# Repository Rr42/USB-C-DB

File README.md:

# USB-C display board for Micro-controllers
This is a mini display board with a USB Type-C connector (carrying USB 2.0) and an onboard micro-controller.

The goal of this display board is to test and evaluate:
* The USB-C interface for a Micro-controller
    * This design uses ESP-WROOM-02
* (TENTATIVE) Implementation of an onboard battery to power the board when disconnected from power
* (TENTATIVE) Onboard battery charging capability using USB-C

## Design overview
### Connecting and booting
To connect to the display board, simply connect it to power and connect to the WiFi network `USB-C DB` it hosts.

Once connected navigate to [http://192.168.1.1](http://192.168.1.1/) and click/press `Play boot animation`.

Once the boot animation plays the page will reload with all the functions enabled.

## Power consumption
The USB-C display board consumes anywhere from `450mW` to a maximum of `800mW` depending on the brightness level from 5V USB.
> Note that the display board does not have the capability and will not negotiate to any of the higher voltage levels offered by USB PD

For context a `500mAh` battery will be able to power the display board for about `3.5 hours` (with maximum power level of `800mW`) and about `5.5 hours` (at the lower `450mW` power level).

### Main page

### Display controller hierarchy

## License
The Software and firmware of this project is licensed under the the MIT license and the hardware is under the [Open Source Hardware](https://www.oshwa.org/definition/) license.

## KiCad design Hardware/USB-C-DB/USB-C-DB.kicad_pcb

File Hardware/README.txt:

# Read me for the USB-C display board hardware
This is a mini display board with a USB Type-C connector (carrying USB 2.0) and an onboard micro-controller.

This project is created using KiCAD (v5.1.10).

The goal of this display board is to test and evaluate:
* The USB-C interface for a Micro-controller
    * This design uses ESP-WROOM-02
* (TENTATIVE) Implementation of an onboard battery to power the board when disconnected from power
* (TENTATIVE) Onboard battery charging capability using USB-C

## License
The Software and firmware of this project is licensed under the the MIT license however the hardware is under the [Open Source Hardware](https://www.oshwa.org/definition/) license.

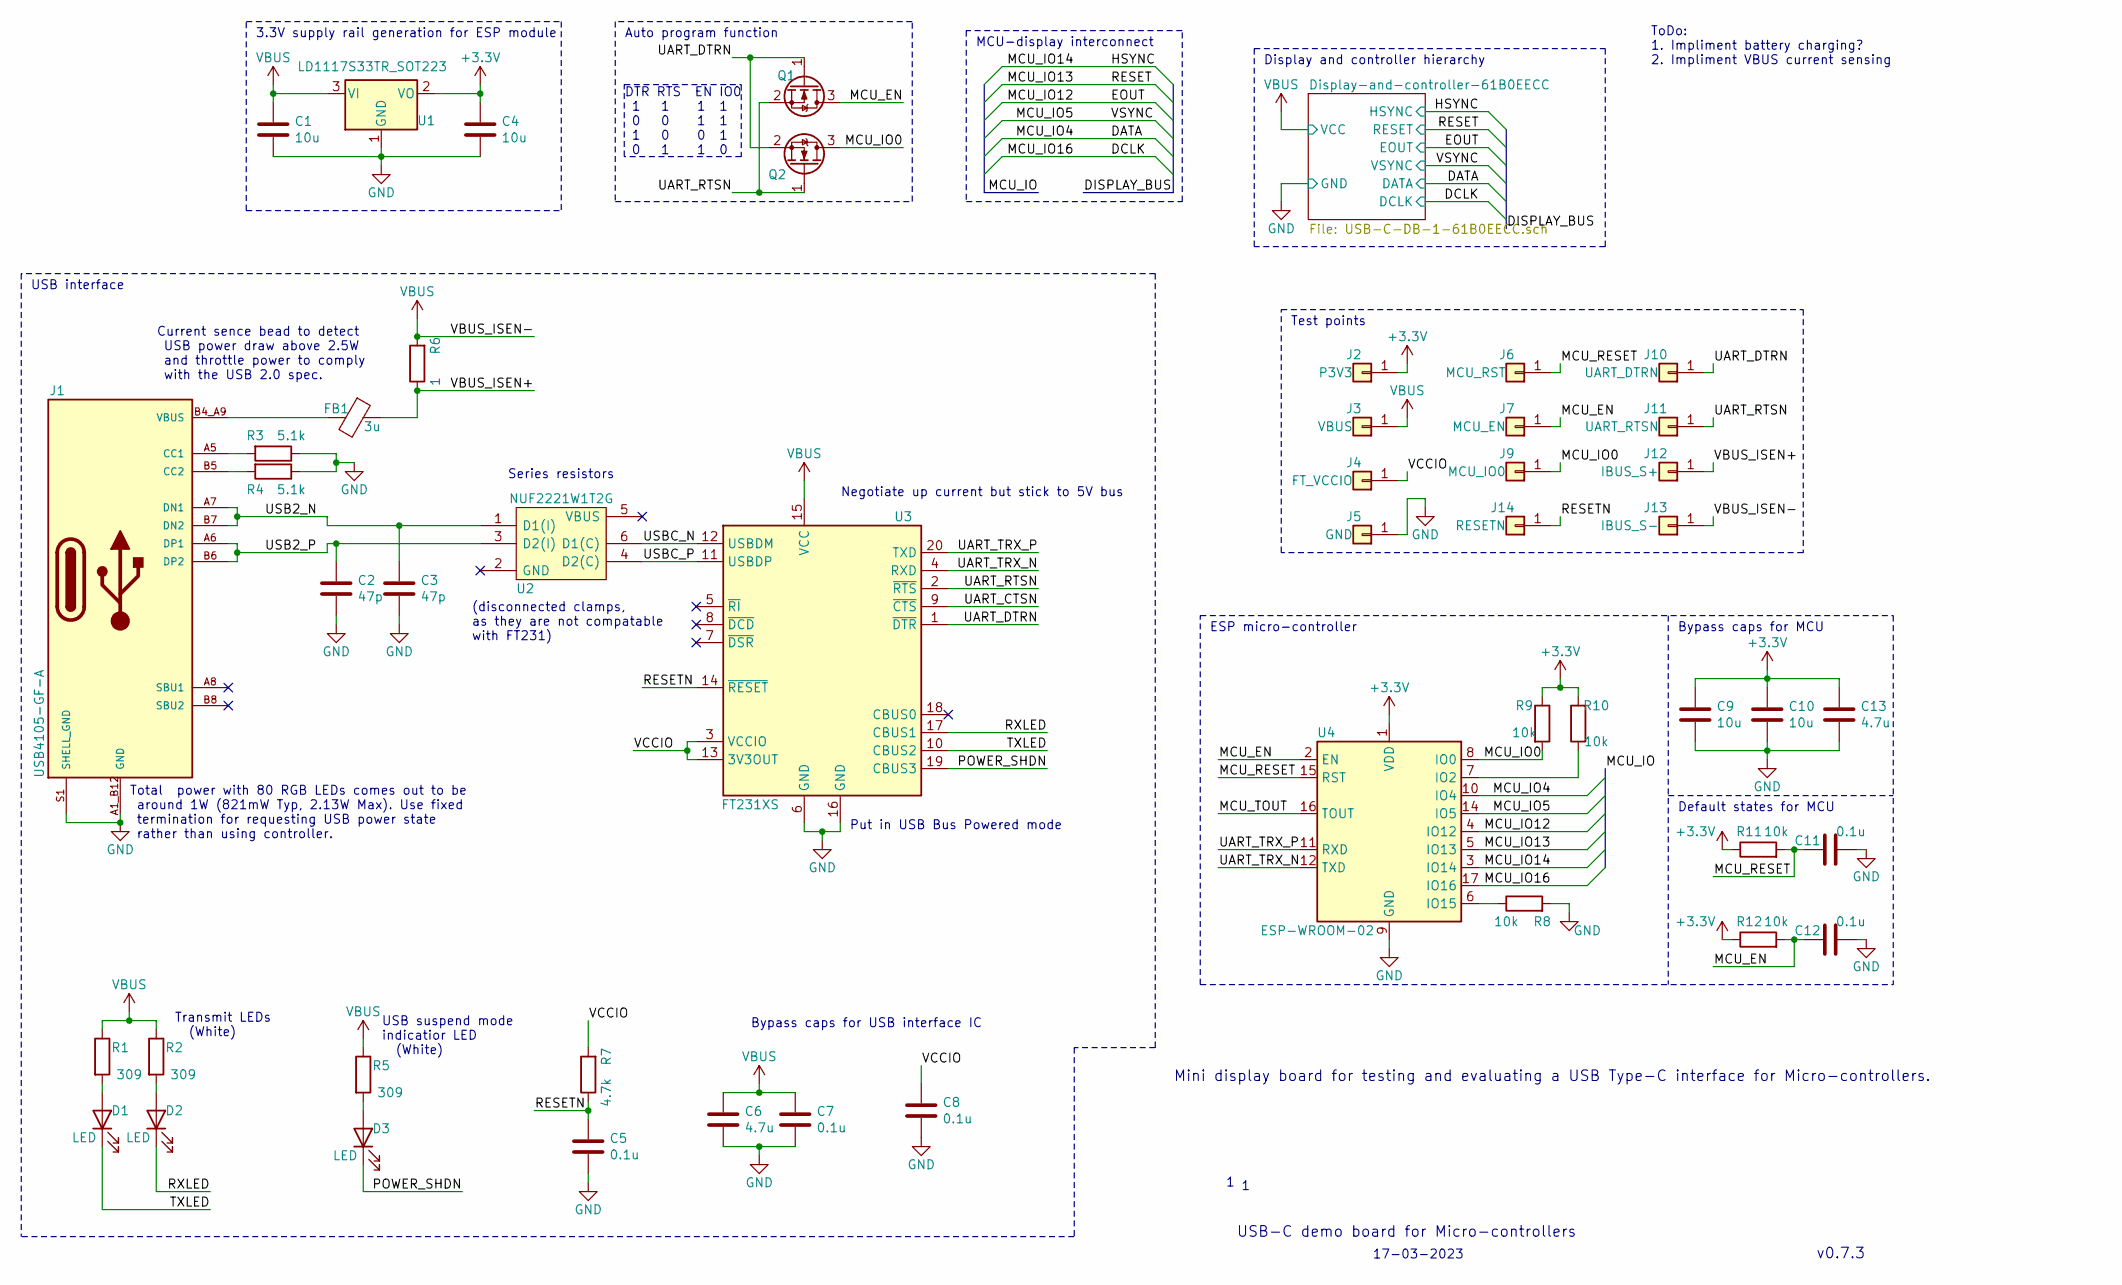
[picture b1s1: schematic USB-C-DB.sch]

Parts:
C1, C4, C9, C10: 10u; C_0805_2012Metric_Pad1.18x1.45mm_HandSolder; MPN CL21A106KOQNNNE
C2, C3: 47p; C_0402_1005Metric_Pad0.74x0.62mm_HandSolder; MPN C0402C470J5GAC
C5, C7, C8, C11, C12: 0.1u; C_0805_2012Metric_Pad1.18x1.45mm_HandSolder; MPN C0805C104M5RAC
C6, C13: 4.7u; C_0805_2012Metric_Pad1.18x1.45mm_HandSolder; MPN CL21A475KAQNNNF
D1, D2, D3: LED; LED_Cree-PLCC4_3.2x2.8mm_CCW; MPN CLA1A-WKB-CWbYa153
FB1: 3u; R_0603_1608Metric_Pad0.98x0.95mm_HandSolder; MPN KPZ1608SHR601ATD25
J1: USB4105-GF-A; GCT_USB4105-GF-A; PARTREV A3
J2: P3V3; TestPoint_Pad_D1.0mm
J3: VBUS; TestPoint_Pad_D1.0mm
J4: FT_VCCIO; TestPoint_Pad_D1.0mm
J5: GND; TestPoint_Pad_D1.0mm
J6: MCU_RST; TestPoint_Pad_D1.0mm
J7: MCU_EN; TestPoint_Pad_D1.0mm
J9: MCU_IO0; TestPoint_Pad_D1.0mm
J10: UART_DTRN; TestPoint_Pad_D1.0mm
J11: UART_RTSN; TestPoint_Pad_D1.0mm
J12: IBUS_S+; TestPoint_Pad_D1.0mm
J13: IBUS_S-; TestPoint_Pad_D1.0mm
J14: RESETN; TestPoint_Pad_D1.0mm
Q1, Q2: XP262N7002TR-G; SOT-23; MPN XP262N7002TR-G
R1, R2, R5: 309; R_0603_1608Metric_Pad0.98x0.95mm_HandSolder; MPN RC0603FR-07309RL
R3, R4: 5.1k; R_0805_2012Metric_Pad1.20x1.40mm_HandSolder; MPN TR0805KR-075K1L
R6: 1; R_0603_1608Metric_Pad0.98x0.95mm_HandSolder; MPN RT0603DRE071RL
R7: 4.7k; R_0805_2012Metric_Pad1.20x1.40mm_HandSolder; MPN RC0805FR-074K7P
R8, R9, R10, R11, R12: 10k; R_0603_1608Metric_Pad0.98x0.95mm_HandSolder; MPN CRG0603F10K/10
U1: LD1117S33TR_SOT223; SOT-223-3_TabPin2; MPN LD1117S33CTR
U2: NUF2221W1T2G; SOT65P210X110-6N; Mouser Part Number 863-NUF2221W1T2G
U3: FT231XS; SSOP-20_3.9x8.7mm_P0.635mm; MPN FT231XS-R; Mouser Part Number 895-FT231XS-R
U4: ESP-WROOM-02; MPN ESP-WROOM-02D-N2

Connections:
+3V3: C4.1, C9.1, C10.1, C13.1, J2.1, R9.1, R10.2, R11.1, R12.1, U1.2 (VO), U4.1 (VDD)
/DATA: U4.10 (IO4); also elsewhere on the board
/DCLK: U4.17 (IO16); also elsewhere on the board
/EOUT: U4.4 (IO12); also elsewhere on the board
/HSYNC: U4.3 (IO14); also elsewhere on the board
/MCU_EN: C12.1, J7.1, Q1.3 (D), R12.2, U4.2 (EN)
/MCU_IO0: J9.1, Q2.3 (D), R9.2, U4.8 (IO0)
/MCU_IO5: U4.14 (IO5); also elsewhere on the board
/MCU_IO13: U4.5 (IO13); also elsewhere on the board
/MCU_RESET: C11.1, J6.1, R11.2, U4.15 (RST)
/MCU_TOUT: U4.16 (TOUT)
/POWER_SHDN: D3.4 (K), U3.19 (CBUS3)
/RESETN: C5.1, J14.1, R7.1, U3.14 (~RESET)
/RXLED: D2.4 (K), U3.17 (CBUS1)
/TXLED: D1.4 (K), U3.10 (CBUS2)
/UART_CTSN: U3.9 (~CTS)
/UART_DTRN: J10.1, Q1.1 (G), Q2.2 (S), U3.1 (~DTR)
/UART_RTSN: J11.1, Q1.2 (S), Q2.1 (G), U3.2 (~RTS)
/UART_TRX_N: U3.4 (RXD), U4.12 (TXD)
/UART_TRX_P: U3.20 (TXD), U4.11 (RXD)
/USB2_N: C3.1, J1.A7 (DN1), J1.B7 (DN2), U2.1 (D1(I))
/USB2_P: C2.1, J1.A6 (DP1), J1.B6 (DP2), U2.3 (D2(I))
/USBC_N: U2.6 (D1(C)), U3.12 (USBDM)
/USBC_P: U2.4 (D2(C)), U3.11 (USBDP)
/VBUS_ISEN+: FB1.1, J12.1, R6.1
/VCCIO: C8.1, J4.1, R7.2, U3.3 (VCCIO), U3.13 (3V3OUT)
GND: C1.2, C2.2, C3.2, C4.2, C5.2, C6.2, C7.2, C8.2, C9.2, C10.2, C11.2, C12.2, C13.2, J1.A1_B12 (GND), J1.B1_A12 (GND), J1.S1 (SHELL_GND), J1.S2 (SHELL_GND), J1.S3 (SHELL_GND), J1.S4 (SHELL_GND), J5.1, R3.1, R4.1, R8.2, U1.1 (GND), U3.6 (GND), U3.16 (GND), U4.9 (GND), U4.13 (GND), U4.18 (GND), U4.19 (GND); also elsewhere on the board
unnamed: D1.2 (A), R1.2
unnamed: D2.2 (A), R2.2
unnamed: D3.2 (A), R5.2
unnamed: J1.A5 (CC1), R3.2
unnamed: J1.B5 (CC2), R4.2
unnamed: R8.1, U4.6 (IO15)
unnamed: R10.1, U4.7 (IO2)

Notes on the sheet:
USB-C demo board for Micro-controllers
v0.7.3
17-03-2023
Mini display board for testing and evaluating a USB Type-C interface for Micro-controllers.
Total power with 80 RGB LEDs comes out to be around 1W (821mW Typ, 2.13W Max). Use fixed termination for requesting USB power state rather than using controller.
Current sence bead to detect USB power draw above 2.5W and throttle power to comply with the USB 2.0 spec.
Display and controller hierarchy
Series resistors
Bypass caps for USB interface IC
USB interface
Auto program function
DTR RTS EN IO0 1 1 1 1 0 0 1 1 1 0 0 1 0 1 1 0
MCU-display interconnect
3.3V supply rail generation for ESP module
Test points
Default states for MCU
ESP micro-controller
Bypass caps for MCU
ToDo: 1. Impliment battery charging? 2. Impliment VBUS current sensing
Negotiate up current but stick to 5V bus
Put in USB Bus Powered mode
Transmit LEDs (White)
USB suspend mode indicatior LED (White)
(disconnected clamps, as they are not compatable with FT231)

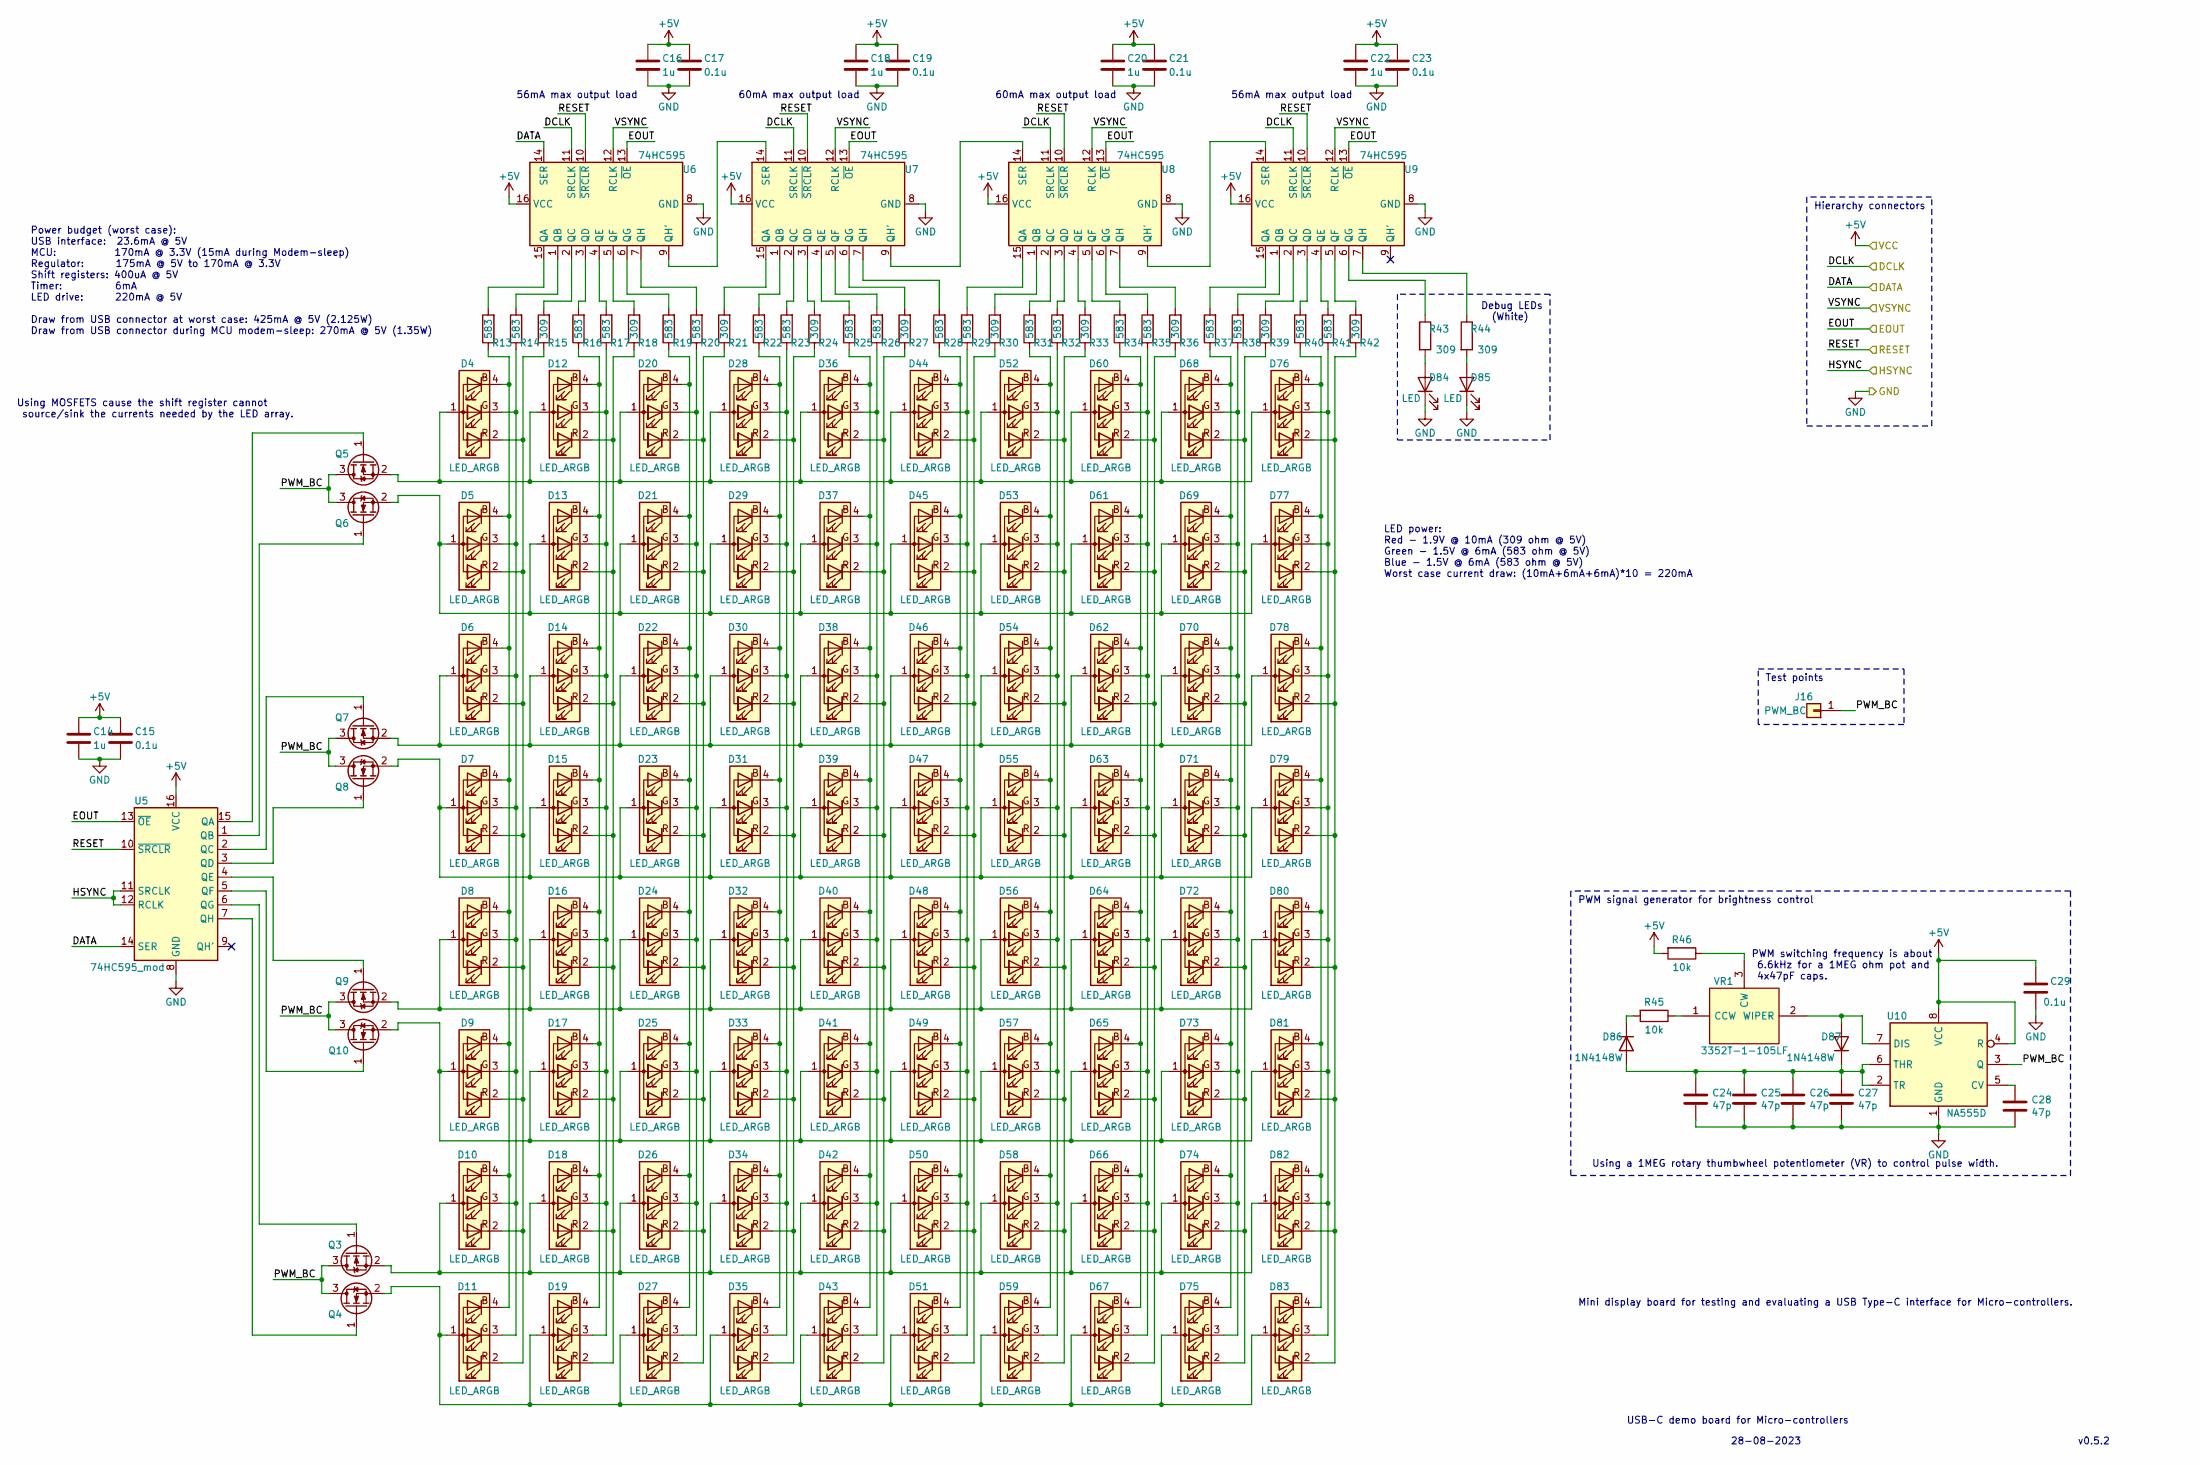
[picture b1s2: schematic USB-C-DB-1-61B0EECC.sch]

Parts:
C14, C16, C18, C20, C22: 1u; C_0805_2012Metric_Pad1.18x1.45mm_HandSolder; MPN CL21B105KBFNNNG
C15, C17, C19, C21, C23, C29: 0.1u; C_0805_2012Metric_Pad1.18x1.45mm_HandSolder; MPN C0805C104M5RAC
C24, C25, C26, C27, C28: 47p; C_0402_1005Metric_Pad0.74x0.62mm_HandSolder; MPN C0402C470J5GAC
D4, D5, D6, D7, D8, D9, D10, D11, D12, D13, D14, D15, D16, D17, D18, D19, D20, D21, D22, D23, D24, D25, D26, D27, D28, D29, D30, D31, D32, D33, D34, D35, D36, D37, D38, D39, D40, D41, D42, D43, D44, D45, D46, D47, D48, D49, D50, D51, D52, D53, D54, D55, D56, D57, D58, D59, D60, D61, D62, D63, D64, D65, D66, D67, D68, D69, D70, D71, D72, D73, D74, D75, D76, D77, D78, D79, D80, D81, D82, D83: LED_ARGB; LED_Cree-PLCC4_3.2x2.8mm_CCW; MPN CLV1L-FKB-CJ1N1E1BB7B3B3
D84, D85: LED; LED_Cree-PLCC4_3.2x2.8mm_CCW; MPN CLA1A-WKB-CWbYa153
D86, D87: 1N4148W; D_SOD-123; MPN 1N4148W_R1_00001
J16: PWM_BC; TestPoint_Pad_D1.0mm
Q3, Q4, Q5, Q6, Q7, Q8, Q9, Q10: XP262N7002TR-G; SOT-23; MPN XP262N7002TR-G
R13, R14, R16, R17, R19, R20, R22, R23, R25, R26, R28, R29, R31, R32, R34, R35, R37, R38, R40, R41: 583; R_0603_1608Metric_Pad0.98x0.95mm_HandSolder; MPN RT0603DRE07583RL
R15, R18, R21, R24, R27, R30, R33, R36, R39, R42, R43, R44: 309; R_0603_1608Metric_Pad0.98x0.95mm_HandSolder; MPN RC0603FR-07309RL
R45, R46: 10k; R_0603_1608Metric_Pad0.98x0.95mm_HandSolder; MPN CRG0603F10K/10
U5: 74HC595_mod; TSSOP-16_4.4x5mm_P0.65mm; MPN MC74HC595ADTG
U6, U7, U8, U9: 74HC595; TSSOP-16_4.4x5mm_P0.65mm; MPN MC74HC595ADTG
U10: NA555D; SOIC-8_3.9x4.9mm_P1.27mm; MPN NA555DR
VR1: 3352T-1-105LF; 3352T1103LF; Mouser Part Number 652-3352T-1-105LF

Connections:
/DATA: U5.14 (SER), U6.14 (SER); also elsewhere on the board
/DCLK: U6.11 (SRCLK), U7.11 (SRCLK), U8.11 (SRCLK), U9.11 (SRCLK); also elsewhere on the board
/Display-and-controller-61B0EECC/PWM_BC: J16.1, Q3.3 (D), Q4.3 (D), Q5.3 (D), Q6.3 (D), Q7.3 (D), Q8.3 (D), Q9.3 (D), Q10.3 (D), U10.3 (Q)
/EOUT: U5.13 (~OE), U6.13 (~OE), U7.13 (~OE), U8.13 (~OE), U9.13 (~OE); also elsewhere on the board
/HSYNC: U5.11 (SRCLK), U5.12 (RCLK); also elsewhere on the board
/MCU_IO5: U6.12 (RCLK), U7.12 (RCLK), U8.12 (RCLK), U9.12 (RCLK); also elsewhere on the board
/MCU_IO13: U5.10 (~SRCLR), U6.10 (~SRCLR), U7.10 (~SRCLR), U8.10 (~SRCLR), U9.10 (~SRCLR); also elsewhere on the board
GND: C14.2, C15.2, C16.2, C17.2, C18.2, C19.2, C20.2, C21.2, C22.2, C23.2, C24.2, C25.2, C26.2, C27.2, C28.2, C29.2, D84.4 (K), D85.4 (K), U5.8 (GND), U6.8 (GND), U7.8 (GND), U8.8 (GND), U9.8 (GND), U10.1 (GND); also elsewhere on the board
unnamed: C24.1, C25.1, C26.1, C27.1, D86.2 (A), D87.1 (K), U10.2 (TR), U10.6 (THR)
unnamed: C28.1, U10.5 (CV)
unnamed: D10.1 (A), D18.1 (A), D26.1 (A), D34.1 (A), D42.1 (A), D50.1 (A), D58.1 (A), D66.1 (A), D74.1 (A), D82.1 (A), Q3.2 (S)
unnamed: D4.2 (RK), D5.2 (RK), D6.2 (RK), D7.2 (RK), D8.2 (RK), D9.2 (RK), D10.2 (RK), D11.2 (RK), R15.1
unnamed: D4.3 (GK), D5.3 (GK), D6.3 (GK), D7.3 (GK), D8.3 (GK), D9.3 (GK), D10.3 (GK), D11.3 (GK), R14.1
unnamed: D4.4 (BK), D5.4 (BK), D6.4 (BK), D7.4 (BK), D8.4 (BK), D9.4 (BK), D10.4 (BK), D11.4 (BK), R13.1
unnamed: D11.1 (A), D19.1 (A), D27.1 (A), D35.1 (A), D43.1 (A), D51.1 (A), D59.1 (A), D67.1 (A), D75.1 (A), D83.1 (A), Q4.2 (S)
unnamed: D4.1 (A), D12.1 (A), D20.1 (A), D28.1 (A), D36.1 (A), D44.1 (A), D52.1 (A), D60.1 (A), D68.1 (A), D76.1 (A), Q5.2 (S)
unnamed: D12.2 (RK), D13.2 (RK), D14.2 (RK), D15.2 (RK), D16.2 (RK), D17.2 (RK), D18.2 (RK), D19.2 (RK), R18.1
unnamed: D12.3 (GK), D13.3 (GK), D14.3 (GK), D15.3 (GK), D16.3 (GK), D17.3 (GK), D18.3 (GK), D19.3 (GK), R17.1
unnamed: D12.4 (BK), D13.4 (BK), D14.4 (BK), D15.4 (BK), D16.4 (BK), D17.4 (BK), D18.4 (BK), D19.4 (BK), R16.1
unnamed: D5.1 (A), D13.1 (A), D21.1 (A), D29.1 (A), D37.1 (A), D45.1 (A), D53.1 (A), D61.1 (A), D69.1 (A), D77.1 (A), Q6.2 (S)
unnamed: D6.1 (A), D14.1 (A), D22.1 (A), D30.1 (A), D38.1 (A), D46.1 (A), D54.1 (A), D62.1 (A), D70.1 (A), D78.1 (A), Q7.2 (S)
unnamed: D7.1 (A), D15.1 (A), D23.1 (A), D31.1 (A), D39.1 (A), D47.1 (A), D55.1 (A), D63.1 (A), D71.1 (A), D79.1 (A), Q8.2 (S)
unnamed: D8.1 (A), D16.1 (A), D24.1 (A), D32.1 (A), D40.1 (A), D48.1 (A), D56.1 (A), D64.1 (A), D72.1 (A), D80.1 (A), Q9.2 (S)
unnamed: D9.1 (A), D17.1 (A), D25.1 (A), D33.1 (A), D41.1 (A), D49.1 (A), D57.1 (A), D65.1 (A), D73.1 (A), D81.1 (A), Q10.2 (S)
unnamed: D20.2 (RK), D21.2 (RK), D22.2 (RK), D23.2 (RK), D24.2 (RK), D25.2 (RK), D26.2 (RK), D27.2 (RK), R21.1
unnamed: D20.3 (GK), D21.3 (GK), D22.3 (GK), D23.3 (GK), D24.3 (GK), D25.3 (GK), D26.3 (GK), D27.3 (GK), R20.1
unnamed: D20.4 (BK), D21.4 (BK), D22.4 (BK), D23.4 (BK), D24.4 (BK), D25.4 (BK), D26.4 (BK), D27.4 (BK), R19.1
unnamed: D28.2 (RK), D29.2 (RK), D30.2 (RK), D31.2 (RK), D32.2 (RK), D33.2 (RK), D34.2 (RK), D35.2 (RK), R24.1
unnamed: D28.3 (GK), D29.3 (GK), D30.3 (GK), D31.3 (GK), D32.3 (GK), D33.3 (GK), D34.3 (GK), D35.3 (GK), R23.1
unnamed: D28.4 (BK), D29.4 (BK), D30.4 (BK), D31.4 (BK), D32.4 (BK), D33.4 (BK), D34.4 (BK), D35.4 (BK), R22.1
unnamed: D36.2 (RK), D37.2 (RK), D38.2 (RK), D39.2 (RK), D40.2 (RK), D41.2 (RK), D42.2 (RK), D43.2 (RK), R27.1
unnamed: D36.3 (GK), D37.3 (GK), D38.3 (GK), D39.3 (GK), D40.3 (GK), D41.3 (GK), D42.3 (GK), D43.3 (GK), R26.1
unnamed: D36.4 (BK), D37.4 (BK), D38.4 (BK), D39.4 (BK), D40.4 (BK), D41.4 (BK), D42.4 (BK), D43.4 (BK), R25.1
unnamed: D44.2 (RK), D45.2 (RK), D46.2 (RK), D47.2 (RK), D48.2 (RK), D49.2 (RK), D50.2 (RK), D51.2 (RK), R30.1
unnamed: D44.3 (GK), D45.3 (GK), D46.3 (GK), D47.3 (GK), D48.3 (GK), D49.3 (GK), D50.3 (GK), D51.3 (GK), R29.1
unnamed: D44.4 (BK), D45.4 (BK), D46.4 (BK), D47.4 (BK), D48.4 (BK), D49.4 (BK), D50.4 (BK), D51.4 (BK), R28.1
unnamed: D52.2 (RK), D53.2 (RK), D54.2 (RK), D55.2 (RK), D56.2 (RK), D57.2 (RK), D58.2 (RK), D59.2 (RK), R33.1
unnamed: D52.3 (GK), D53.3 (GK), D54.3 (GK), D55.3 (GK), D56.3 (GK), D57.3 (GK), D58.3 (GK), D59.3 (GK), R32.1
unnamed: D52.4 (BK), D53.4 (BK), D54.4 (BK), D55.4 (BK), D56.4 (BK), D57.4 (BK), D58.4 (BK), D59.4 (BK), R31.1
unnamed: D60.2 (RK), D61.2 (RK), D62.2 (RK), D63.2 (RK), D64.2 (RK), D65.2 (RK), D66.2 (RK), D67.2 (RK), R36.1
unnamed: D60.3 (GK), D61.3 (GK), D62.3 (GK), D63.3 (GK), D64.3 (GK), D65.3 (GK), D66.3 (GK), D67.3 (GK), R35.1
unnamed: D60.4 (BK), D61.4 (BK), D62.4 (BK), D63.4 (BK), D64.4 (BK), D65.4 (BK), D66.4 (BK), D67.4 (BK), R34.1
unnamed: D68.2 (RK), D69.2 (RK), D70.2 (RK), D71.2 (RK), D72.2 (RK), D73.2 (RK), D74.2 (RK), D75.2 (RK), R39.1
unnamed: D68.3 (GK), D69.3 (GK), D70.3 (GK), D71.3 (GK), D72.3 (GK), D73.3 (GK), D74.3 (GK), D75.3 (GK), R38.1
unnamed: D68.4 (BK), D69.4 (BK), D70.4 (BK), D71.4 (BK), D72.4 (BK), D73.4 (BK), D74.4 (BK), D75.4 (BK), R37.1
unnamed: D76.2 (RK), D77.2 (RK), D78.2 (RK), D79.2 (RK), D80.2 (RK), D81.2 (RK), D82.2 (RK), D83.2 (RK), R42.1
unnamed: D76.3 (GK), D77.3 (GK), D78.3 (GK), D79.3 (GK), D80.3 (GK), D81.3 (GK), D82.3 (GK), D83.3 (GK), R41.1
unnamed: D76.4 (BK), D77.4 (BK), D78.4 (BK), D79.4 (BK), D80.4 (BK), D81.4 (BK), D82.4 (BK), D83.4 (BK), R40.1
unnamed: D84.2 (A), R43.2
unnamed: D85.2 (A), R44.2
unnamed: D86.1 (K), R45.2
unnamed: D87.2 (A), U10.7 (DIS), VR1.2 (WIPER)
unnamed: Q3.1 (G), U5.6 (QG)
unnamed: Q4.1 (G), U5.7 (QH)
unnamed: Q5.1 (G), U5.15 (QA)
unnamed: Q6.1 (G), U5.1 (QB)
unnamed: Q7.1 (G), U5.2 (QC)
unnamed: Q8.1 (G), U5.3 (QD)
unnamed: Q9.1 (G), U5.4 (QE)
unnamed: Q10.1 (G), U5.5 (QF)
unnamed: R13.2, U6.15 (QA)
unnamed: R14.2, U6.1 (QB)
unnamed: R15.2, U6.2 (QC)
unnamed: R16.2, U6.3 (QD)
unnamed: R17.2, U6.4 (QE)
unnamed: R18.2, U6.5 (QF)
unnamed: R19.2, U6.6 (QG)
unnamed: R20.2, U6.7 (QH)
unnamed: R21.2, U7.15 (QA)
unnamed: R22.2, U7.1 (QB)
unnamed: R23.2, U7.2 (QC)
unnamed: R24.2, U7.3 (QD)
unnamed: R25.2, U7.4 (QE)
unnamed: R26.2, U7.5 (QF)
unnamed: R27.2, U7.6 (QG)
unnamed: R28.2, U7.7 (QH)
unnamed: R29.2, U8.15 (QA)
unnamed: R30.2, U8.1 (QB)
unnamed: R31.2, U8.2 (QC)
unnamed: R32.2, U8.3 (QD)
unnamed: R33.2, U8.4 (QE)
unnamed: R34.2, U8.5 (QF)
unnamed: R35.2, U8.6 (QG)
unnamed: R36.2, U8.7 (QH)
unnamed: R37.2, U9.15 (QA)
unnamed: R38.2, U9.1 (QB)
unnamed: R39.2, U9.2 (QC)
unnamed: R40.2, U9.3 (QD)
unnamed: R41.2, U9.4 (QE)
unnamed: R42.2, U9.5 (QF)
unnamed: R43.1, U9.6 (QG)
unnamed: R44.1, U9.7 (QH)
unnamed: R45.1, VR1.1 (CCW)
unnamed: R46.1, VR1.3 (CW)
unnamed: U6.9 (QH'), U7.14 (SER)
unnamed: U7.9 (QH'), U8.14 (SER)
unnamed: U8.9 (QH'), U9.14 (SER)

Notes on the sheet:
USB-C demo board for Micro-controllers
28-08-2023
v0.5.2
Debug LEDs (White)
LED power: Red - 1.9V @ 10mA (309 ohm @ 5V) Green - 1.5V @ 6mA (583 ohm @ 5V) Blue - 1.5V @ 6mA (583 ohm @ 5V) Worst case current draw: (10mA+6mA+6mA)*10 = 220mA
Mini display board for testing and evaluating a USB Type-C interface for Micro-controllers.
Hierarchy connectors
Power budget (worst case): USB interface: 23.6mA @ 5V MCU: 170mA @ 3.3V (15mA during Modem-sleep) Regulator: 175mA @ 5V to 170mA @ 3.3V Shift registers: 400uA @ 5V Timer: 6mA LED drive: 220mA @ 5V Draw from USB connector at worst case: 425mA @ 5V (2.125W) Draw from USB connector during MCU modem-sl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
Using MOSFETS cause the shift register cannot source/sink the currents needed by the LED array.
Using a 1MEG rotary thumbwheel potentiometer (VR) to control pulse width.
PWM switching frequency is about 6.6kHz for a 1MEG ohm pot and 4x47pF caps.
PWM signal generator for brightness control
Test points
60mA max output load
56mA max output load

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
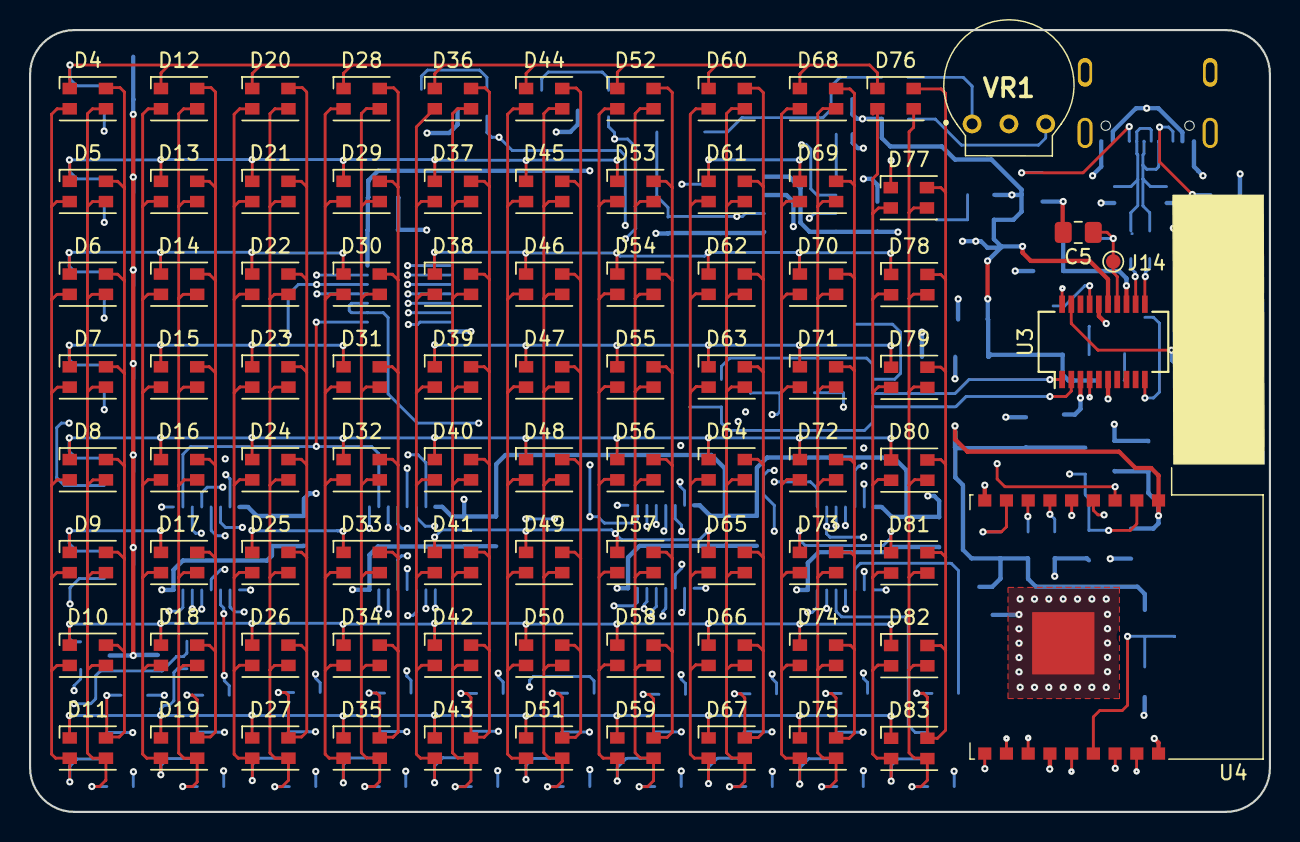
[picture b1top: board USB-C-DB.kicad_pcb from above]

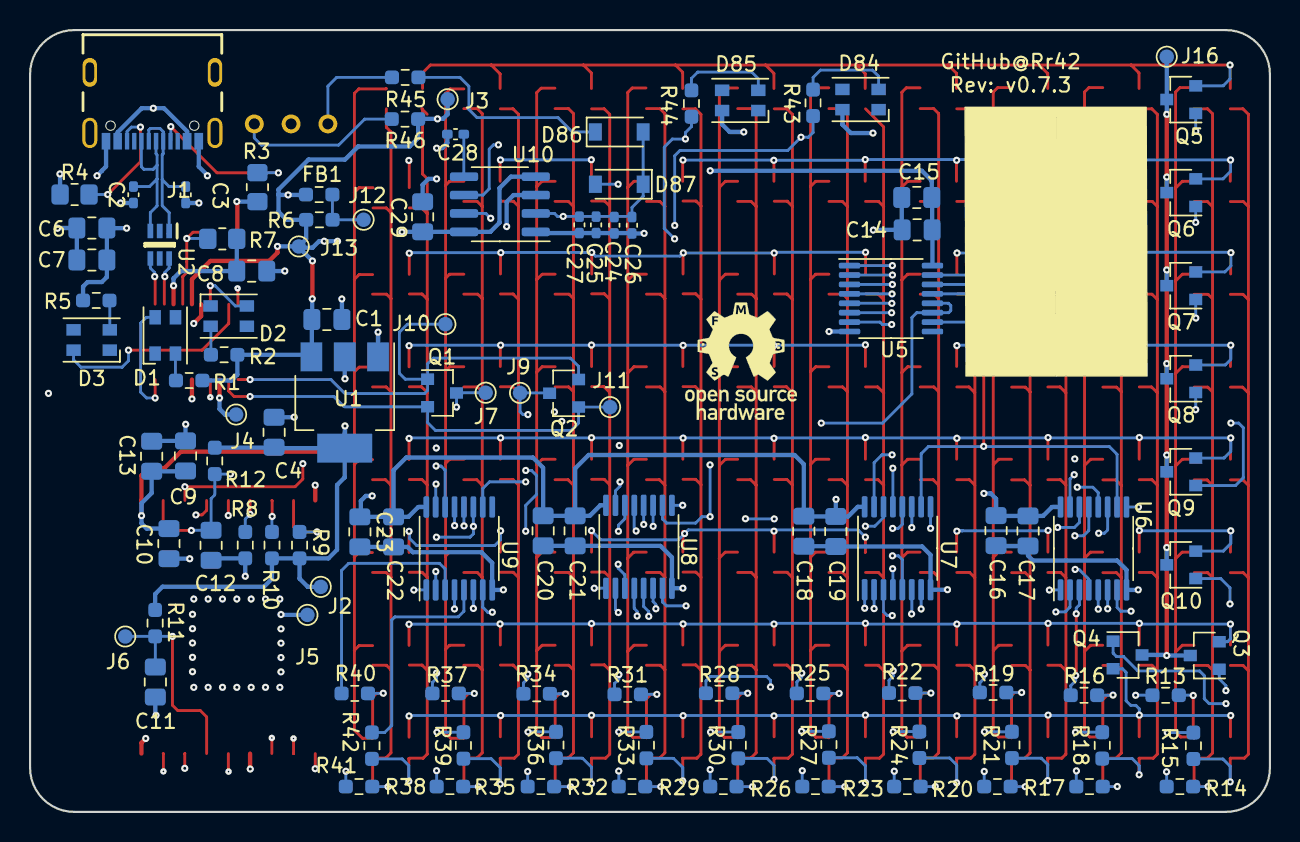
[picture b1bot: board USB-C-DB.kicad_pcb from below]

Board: 4 copper layers, 85.6 x 54.0 mm, 199 parts (114 on the bottom side), 123 nets.

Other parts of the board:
G1: LOGO; oshw-spfmb

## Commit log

2021-08-29 First commit > Adding Readme for repository > Adding Lcense for repository > Adding placeholder KiCAD project
2021-12-17 Updating schematic to v0.2 > Added USB to UART bridge and initial biasing > Added biasing circuitry for MCU > Moved display section to hierarchy > Simplified and consolidated power supply section > A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
2022-02-12 Wiring up USB interface (schematic v0.3) > Adding ESD circuity for USB interface > Adding remaining bias and configuration circuity for the UBS interface IC
2022-02-21 Adding PWM based brightness control circuit for display
2022-02-22 Adding LED array to display subsection
2022-02-23 Wiring up display subsection
2022-03-08 Adding auto program functionality
    > Adding OSHW logo to schematics
    > Adding Test points for select signals
    > Updating README with schematic images
2022-03-08 Minor corrections in README
    Fixing schematic image paths.
2022-03-09 Cleaning up schematic after power budgeting
2022-03-11 Finalizing schematic for BOM analysis
    * Replacing MOSFET parts with higher current version.
    * Re-adding 555 based brightness control circuit.
2022-03-16 Updating with alternative parts
2022-03-17 Adding OSHW logo on PCB
    * Updating BOM with available parts for test run
2022-03-21 Adding full layout for design
2022-03-22 Updating layout with version info
2022-08-28 Updating schematic to replace FT260 for FT231
2022-09-05 Updating layout to replace FT260 for FT231
2022-11-01 Fixing incorrect connection in debug LEDs
    * Updating symbol to fix incorrect GND connection in debug LED
    * Adding image of assembled demo
2022-11-01 Adding sample firmware
2022-11-08 Renaming display library and adding default constructor
    * Reordering color frame argument order
    * Correcting bit frame size to 10 from 11
2022-11-08 Adding placeholder firmware
2022-12-04 Updating readme
2022-12-09 Adding 3D model for printable case
2022-12-19 Patching bug where ESP8266 would soft reset while displaying long sequences
    * Replacing delayMicroseconds with optimistic_yield to allow the softAP to do its thing during the delay preventing resets
2022-12-19 Updating firmware with boot animation
    * Adding boot animation and display modes
    * Adding bouncy ball screen saver as display mode 9
2023-01-18 Updating case design dial and adding readme for software section
    * Updating case design to prevent minor collision with brightness dial
    * Adding a common README for USB-C DB's software and firmware
    * Adding connection and power information to main README
2023-02-19 Adding HTML placeholder for custom lighting table
2023-02-20 Adding functional custom mode
    * Adding separate custom mode page with Ajax callbacks allowing back communication from HTML client to the display board
    * Adding reference HTML files
2023-02-20 Adding demo video for firmware
2023-02-27 Adding placeholder for frame builder tool
2023-02-28 Moving library definitions and functions to septate file
    * Migrated all class definitions and implementations to DBframe.py
    * Cleaned up main frame-builder.py for managing UI
2023-03-17 Patching activity LED connections and adding FTDI firmware
    * Patching issue in layout where the FTDI activity LED orientations where incorrectly connected.
    * Adding firmware template and instructions to modify the FT231's EEPROM firmware
2023-05-18 Updating schematic SVGs to latest version
2023-08-28 Updating OSHW logo to include mechanicals
2024-01-04 Adding implementation for custom frame builder
    * Adding transpose function to DBframe library
    * Adding frame builder UI framework
    * Adding UI based frame builder tool
    * Updating software readme with frame builder instructions
